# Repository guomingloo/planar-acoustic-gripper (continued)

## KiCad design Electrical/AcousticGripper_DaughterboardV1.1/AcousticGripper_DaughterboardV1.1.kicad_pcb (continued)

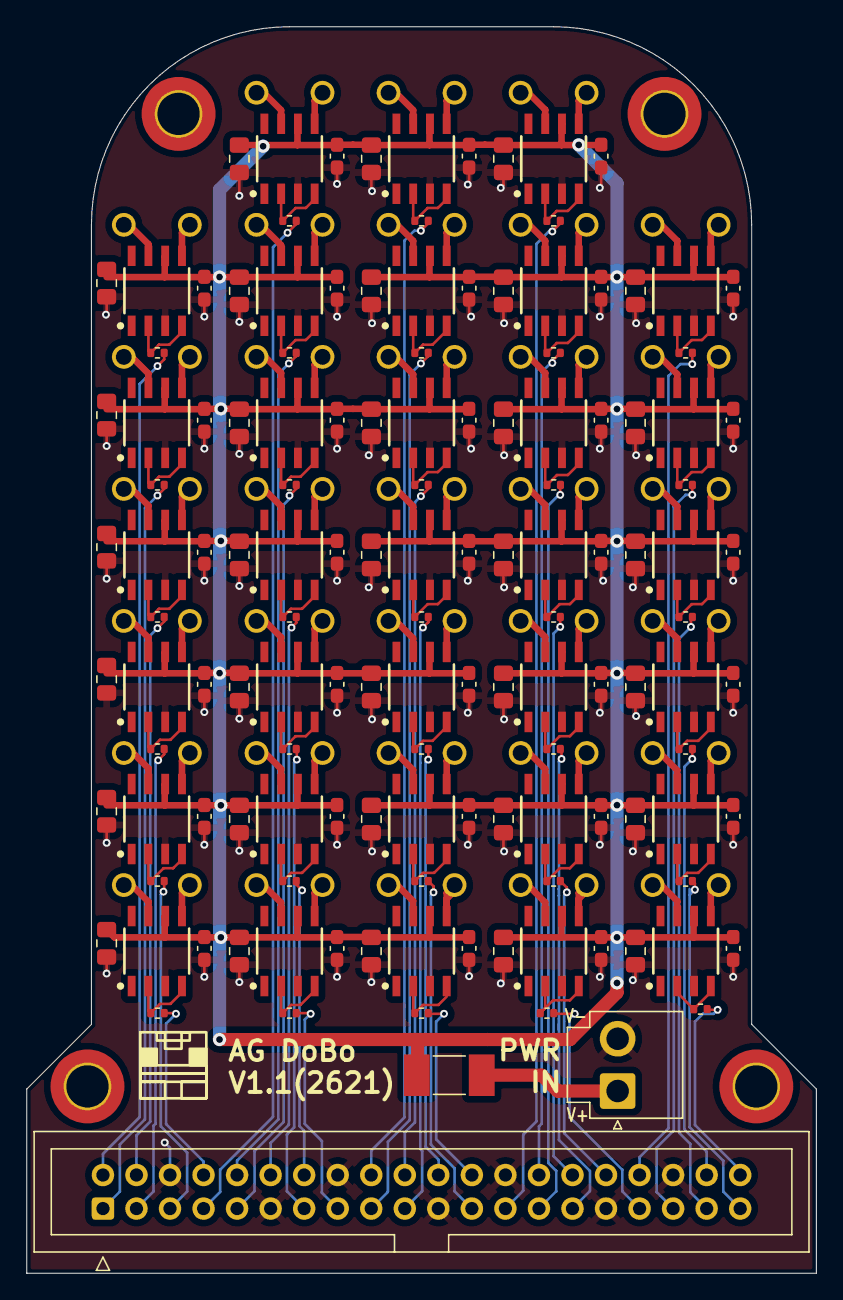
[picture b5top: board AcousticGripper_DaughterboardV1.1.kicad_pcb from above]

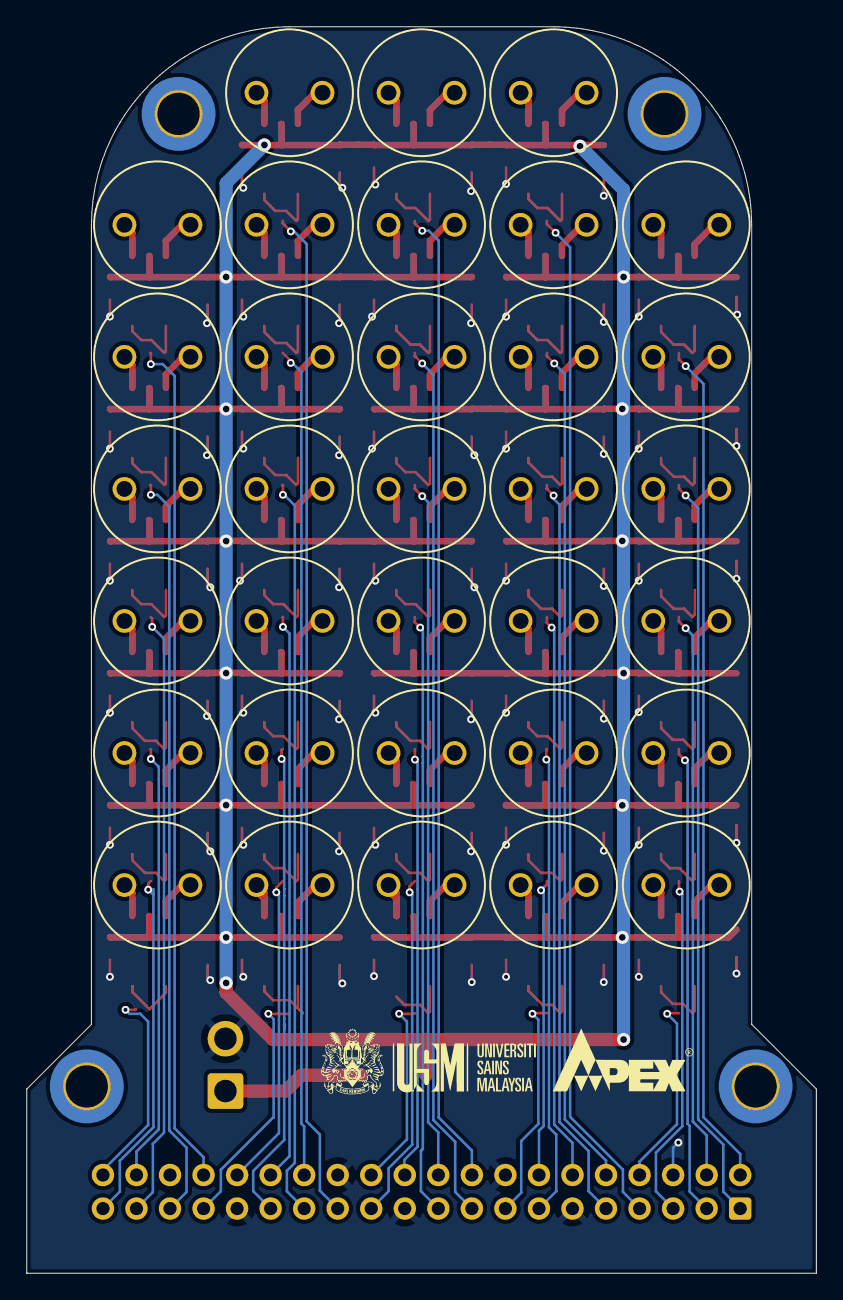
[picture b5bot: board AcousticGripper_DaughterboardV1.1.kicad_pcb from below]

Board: 2 copper layers, 59.8 x 94.4 mm, 168 parts (33 on the bottom side), 135 nets.

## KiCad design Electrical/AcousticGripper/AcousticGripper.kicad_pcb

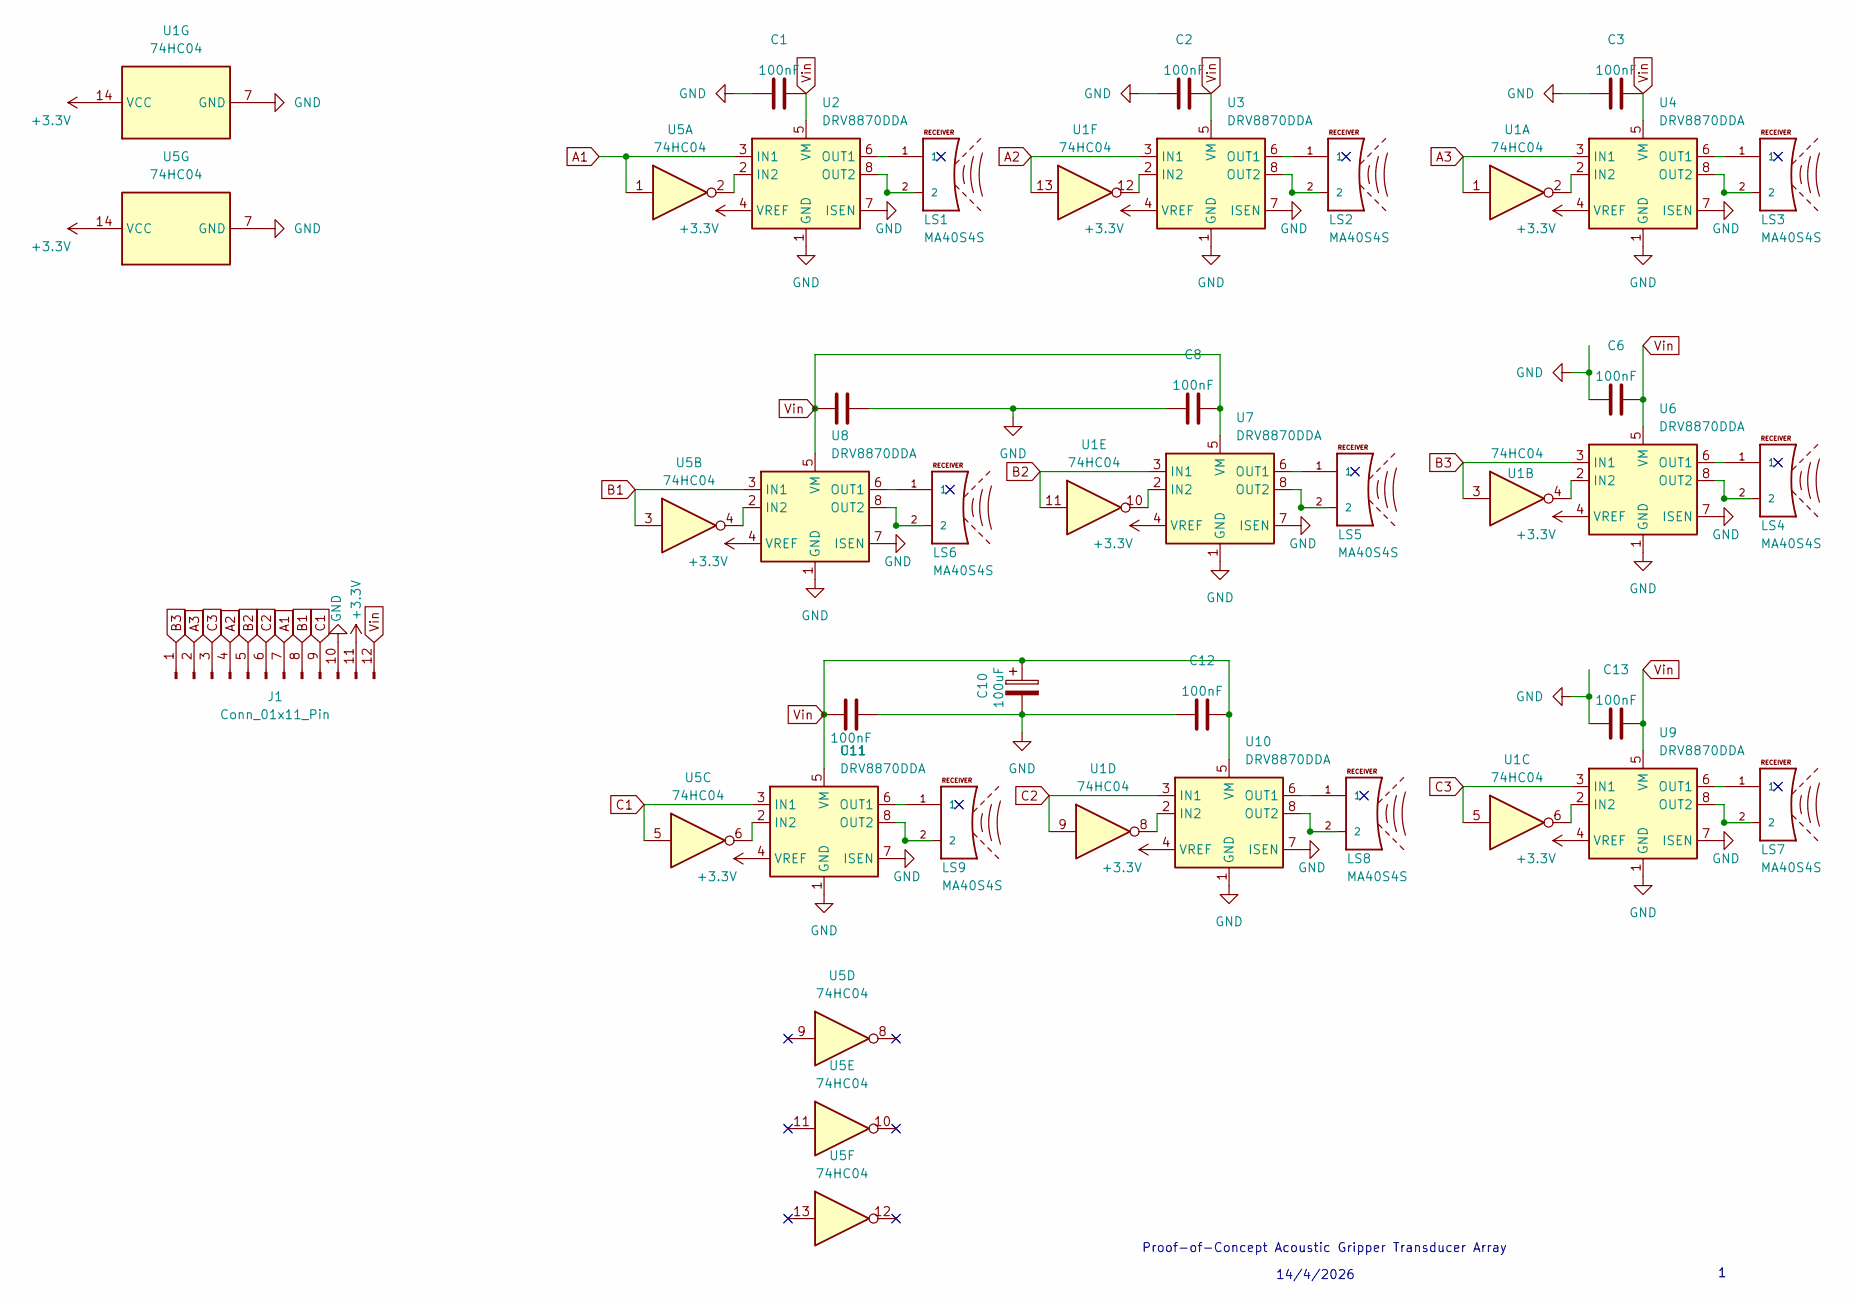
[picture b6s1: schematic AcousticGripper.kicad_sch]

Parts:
C1, C2, C3, C6, C7, C8, C11, C12, C13: 100nF; C_0603_1608Metric_Pad1.08x0.95mm_HandSolder
C10: 100uF; CP_Radial_D8.0mm_P3.50mm
J1: Conn_01x11_Pin; PinHeader_1x12_P2.54mm_Vertical
LS1, LS2, LS3, LS4, LS5, LS6, LS7, LS8, LS9: MA40S4S; XDCR_MA40S4S
U1, U5: 74HC04; SOIC-14_3.9x8.7mm_P1.27mm
U2, U3, U4, U6, U7, U8, U9, U10, U11: DRV8870DDA; VREG_LM5017MR_NOPB

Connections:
+3.3V: J1.11, U1.14 (VCC), U2.4 (VREF), U3.4 (VREF), U4.4 (VREF), U5.14 (VCC), U6.4 (VREF), U7.4 (VREF), U8.4 (VREF), U9.4 (VREF), U10.4 (VREF), U11.4 (VREF)
A1: J1.7, U2.3 (IN1), U5.1
A2: J1.4, U1.13, U3.3 (IN1)
A3: J1.2, U1.1, U4.3 (IN1)
B1: J1.8, U5.3, U8.3 (IN1)
B2: J1.5, U1.11, U7.3 (IN1)
B3: J1.1, U1.3, U6.3 (IN1)
C1: J1.9, U5.5, U11.3 (IN1)
C2: J1.6, U1.9, U10.3 (IN1)
C3: J1.3, U1.5, U9.3 (IN1)
GND: C1.1, C2.1, C3.1, C6.1, C7.2, C8.1, C10.2, C11.1, C12.1, C13.1, J1.10, U1.7 (GND), U2.1 (GND), U2.7 (ISEN), U2.9 (GND), U3.1 (GND), U3.7 (ISEN), U3.9 (GND), U4.1 (GND), U4.7 (ISEN), U4.9 (GND), U5.7 (GND), U6.1 (GND), U6.7 (ISEN), U6.9 (GND), U7.1 (GND), U7.7 (ISEN), U7.9 (GND), U8.1 (GND), U8.7 (ISEN), U8.9 (GND), U9.1 (GND), U9.7 (ISEN), U9.9 (GND), U10.1 (GND), U10.7 (ISEN), U10.9 (GND), U11.1 (GND), U11.7 (ISEN), U11.9 (GND)
unnamed: U2.2 (IN2), U5.2
unnamed: LS1.1, U2.6 (OUT1)
unnamed: LS1.2, U2.8 (OUT2)
unnamed: U1.12, U3.2 (IN2)
unnamed: LS2.1, U3.6 (OUT1)
unnamed: LS2.2, U3.8 (OUT2)
unnamed: U1.2, U4.2 (IN2)
unnamed: LS3.1, U4.6 (OUT1)
unnamed: LS3.2, U4.8 (OUT2)
unnamed: U1.4, U6.2 (IN2)
unnamed: LS4.1, U6.6 (OUT1)
unnamed: LS4.2, U6.8 (OUT2)
unnamed: U1.10, U7.2 (IN2)
unnamed: LS5.1, U7.6 (OUT1)
unnamed: LS5.2, U7.8 (OUT2)
unnamed: U5.4, U8.2 (IN2)
unnamed: LS6.1, U8.6 (OUT1)
unnamed: LS6.2, U8.8 (OUT2)
unnamed: U1.6, U9.2 (IN2)
unnamed: LS7.1, U9.6 (OUT1)
unnamed: LS7.2, U9.8 (OUT2)
unnamed: U1.8, U10.2 (IN2)
unnamed: LS8.1, U10.6 (OUT1)
unnamed: LS8.2, U10.8 (OUT2)
unnamed: U5.6, U11.2 (IN2)
unnamed: LS9.1, U11.6 (OUT1)
unnamed: LS9.2, U11.8 (OUT2)
Vin: C1.2, C2.2, C3.2, C6.2, C7.1, C8.2, C10.1, C11.2, C12.2, C13.2, J1.12, U2.5 (VM), U3.5 (VM), U4.5 (VM), U6.5 (VM), U7.5 (VM), U8.5 (VM), U9.5 (VM), U10.5 (VM), U11.5 (VM)

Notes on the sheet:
Proof-of-Concept Acoustic Gripper Transducer Array
14/4/2026

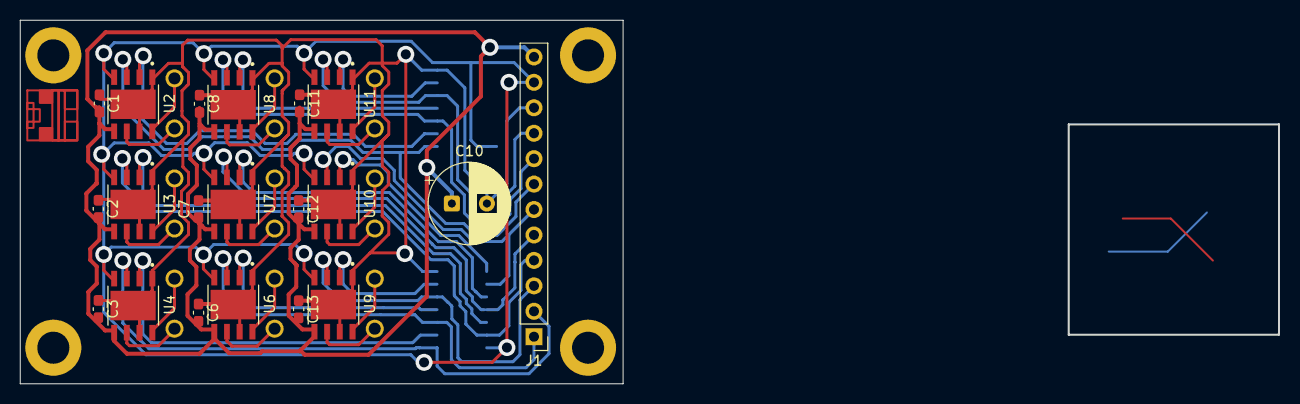
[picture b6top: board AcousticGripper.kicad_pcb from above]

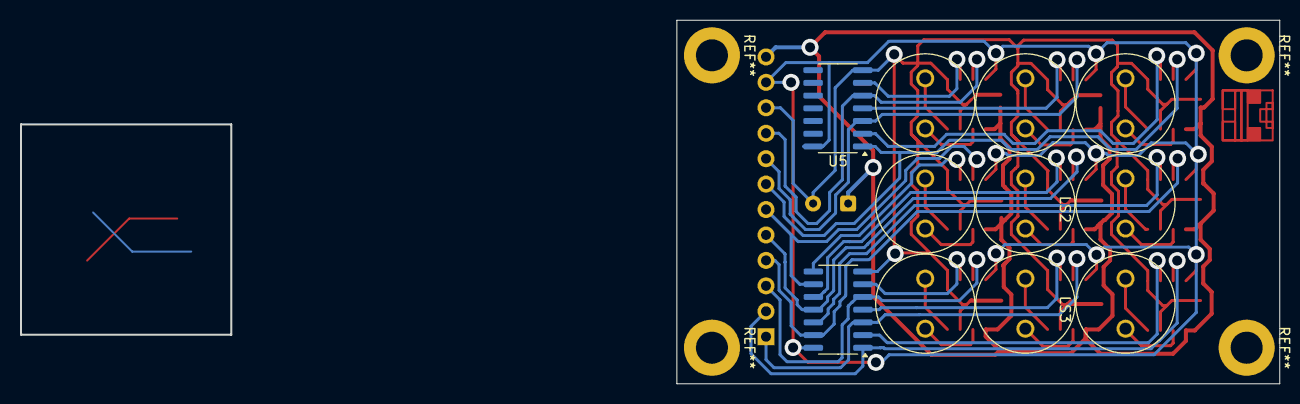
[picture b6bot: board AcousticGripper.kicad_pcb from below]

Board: 2 copper layers, 60.2 x 36.3 mm, 31 parts (11 on the bottom side), 39 nets.
